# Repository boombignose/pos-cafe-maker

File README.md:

<div align="center">

# POS Café Maker
## ระบบร้านคาเฟ่บน Windows พร้อมพิมพ์เขียวเครื่อง POS

**ระบบร้านบน PostgreSQL · หลายหน้าจอใน LAN · ไม่ใช้ Docker · เคส 3D และ KiCad แก้ต่อได้**

แจกแบบ CAD และ source ที่ใช้งานแก้ไขได้ พร้อม [ที่มาข้อมูลและใบบันทึกอุปกรณ์](docs/BLUEPRINT.md) ขนาดจอเริ่มต้นอ้างอิง Waveshare 7inch HDMI LCD (C) จากเอกสารผู้ผลิต บอร์ดทั่วไป/พัดลมเป็นแม่แบบขนาดสมมติ ส่วนขอบบอร์ด รูและ net ของ PCB accessory มาจาก KiCad ใน repo ต้องตรวจอุปกรณ์จริงก่อนผลิต

รุ่น 0.1.2 เก็บมุมเคส ฐานเป็นแท่นรองด้านหลังขันยึดกับฝา มีตัวประคองขอบหลังจอและช่องรัดสาย หน้าขายใช้ปุ่มเมนูแบบข้อความและตะกร้าชำระเงินในพื้นที่จอ 1024×600 ดู [วิธีประกอบ](docs/PRINTING.md) แบบยังไม่ผ่านการประกอบจริง

[เปิดเดโมออนไลน์](https://boombignose.github.io/pos-cafe-maker/) · [เริ่มใช้](#quick-start) · [ออกแบบและพิมพ์](docs/DESIGNER.md) · [วงจรและ PCB](docs/HARDWARE.md) · [ผลตรวจ](docs/TEST-REPORT.md)

[ดาวน์โหลด Source ZIP](https://github.com/boombignose/pos-cafe-maker/archive/refs/heads/main.zip) · [ชุดระบบร้านและเดโม](https://github.com/boombignose/pos-cafe-maker/releases/tag/v0.2.0)

</div>

> **เลือกให้ตรงโหมด:** `shop ZIP` เป็นระบบร้านที่ใช้ฐานข้อมูลกลางและบัญชีจริง ส่วนเว็บ Pages และ `demo ZIP` เป็นข้อมูลจำลองใน browser ทั้งคู่ใช้ซอร์สเดียวกัน แต่แยกชุด build ชัดเจน เคส/PCB ยังไม่ผ่านการผลิตและประกอบจริง

## ใช้ระบบร้านบน Windows

1. ติดตั้ง [Node.js 24 LTS](https://nodejs.org/en/download) และ [PostgreSQL 17 หรือ18](https://www.postgresql.org/download/windows/) จากผู้ผลิต
2. ดาวน์โหลด `pos-cafe-maker-shop-v0.2.0.zip` จาก [Release](https://github.com/boombignose/pos-cafe-maker/releases/tag/v0.2.0) แตกไฟล์ แล้วดับเบิลคลิก **Start.cmd** ครั้งแรกต้องมีอินเทอร์เน็ตเพื่อติดตั้ง npm dependencies ไม่มี API key หรือ Docker
3. ใช้รหัสใน `SETUP-TOKEN.txt` ที่เครื่องร้านตั้งชื่อร้านและบัญชีเจ้าของผ่านเว็บ ไม่มีรหัสเริ่มต้นร่วมกัน เพิ่มวัตถุดิบ/เมนู/บัญชีทีมตามร้านจริง แล้วเปิดกะ
4. เครื่องลูกเปิด URL LAN ที่ Start แสดง ข้อมูลอยู่ PostgreSQL ของเครื่องกลาง รีสตาร์ต/เปลี่ยนโฟลเดอร์โปรแกรมแล้วข้อมูลยังอยู่ สำรองผ่านหน้า **ตั้งค่าร้าน** หรือ Backup.cmd กู้เข้า database ใหม่โดยเก็บต้นฉบับไว้

อ่าน [คู่มือติดตั้ง LAN สำรอง กู้คืน และอัปเดต](docs/INSTALL.md) ก่อนใช้ HTTP ไม่เข้ารหัสข้อมูลระหว่างเครื่อง ใช้เฉพาะเครือข่ายร้านที่เชื่อถือได้หรือให้ผู้ดูแลติดตั้ง HTTPS ผลตรวจโปรแกรมไม่แทนการทดสอบเครื่องพิมพ์และการทดลองร้านของคุณ

สำหรับผู้ที่ต้องการเตรียม Docker มี [คู่มือติดตั้ง Docker Desktop และ WSL 2 บน Windows](docs/DOCKER-WINDOWS.md) พร้อมตรวจ engine/Compose และแก้ปัญหาเบื้องต้น คู่มือนี้ยังไม่ใช่ชุดรัน POS ด้วย Docker; รุ่นนี้ใช้ `Start.cmd` ตามขั้นตอนข้างบน

ภาพเป็นรายการทดสอบบนฐานข้อมูลจริง ไม่ใช่ยอดขายหรือเงินที่รับจากลูกค้าจริง

## ในชุดนี้มีอะไร

| ออกแบบเครื่อง | ลองขายคาเฟ่ | วงจรเสริม | ส่งต่อทำของจริง |
|---|---|---|---|
| ขนาดจอ/เคส · บอร์ด · รูยึด · ช่องพอร์ต · มุมฐาน | เมนู/ตัวเลือก · เงินสด/โอนจำลอง · คิวบาร์ · กะ · สต็อกสูตร · CSV | บอร์ดเสริม 5V · ฟิวส์ · ป้องกันกลับขั้ว · พัดลม · ไฟสถานะ | STL แยก4ชิ้น · JSON · KiCad · BOM · Gerber · drill · STEP |

### ลองเดโม / พัฒนาจากซอร์ส

ต้องมี **Node.js 22.12+ หรือ Node.js 24 LTS** และ npm ไม่ต้องใส่ API key

```sh
git clone https://github.com/boombignose/pos-cafe-maker.git
cd pos-cafe-maker
npm ci
npm run dev
```

1. เปิด URL ที่ Vite แสดง โดยปกติ `http://localhost:5173` แล้วเข้า **ออกแบบเครื่อง** วัดขนาดอุปกรณ์จริงก่อนปรับแบบ
2. เข้า **หน้าขาย POS** → เปิดกะ → เลือกเมนู → รับเงินจำลอง → ออกคิว เลือกบทบาทด้านบนเพื่อลองแคชเชียร์หรือบาร์
3. ดาวน์โหลด STL/JSON จากหน้าออกแบบ เปิดใน slicer และดู [คู่มือ PCB](docs/HARDWARE.md) ก่อนสั่งพิมพ์หรือส่งผลิต

ถ้าดาวน์โหลด Source ZIP ให้แตกไฟล์ เปิด Terminal ในโฟลเดอร์นั้น แล้วเริ่มจาก `npm ci` หน้า HTML ต้องเปิดผ่านเว็บเซิร์ฟเวอร์ ไม่ใช่ดับเบิลคลิกซอร์ส `index.html`

### เดโม browser สำเร็จรูปจาก Release

ดาวน์โหลดไฟล์ `pos-cafe-maker-demo-v0.2.0.zip` แตกไฟล์ แล้วรัน:

```sh
cd pos-cafe-maker-demo
python3 -m http.server 8080 --bind 127.0.0.1
```

เปิด `http://localhost:8080` ไม่มี npm/Docker/ฐานข้อมูลสำหรับแพ็กเกจเดโมที่ build แล้ว ต้องดาวน์โหลดไฟล์นี้จาก Release ไม่ใช่ Source ZIP หน้าเว็บและข้อมูลจำลองทำงานได้โดยไม่ใช้บริการออนไลน์หลังดาวน์โหลด

## ลอง workflow ร้าน

ทั้งโหมดร้านและเดโม หน้าขายเลือกหมวดและเมนู เพิ่มจำนวน เลือกขนาด/ชนิดนม คำนวณเงินทอน และพิมพ์ใบเสร็จตัวอย่าง58/80มม. โหมดร้านพนักงานต้องตรวจยอดโอนจริงก่อนยืนยัน ส่วนเดโมจำลองการตรวจ ไม่มีการเชื่อมธนาคาร

คิวบาร์อัปเดตทุก2วินาที เริ่มทำ → พร้อมรับ → ส่งมอบ เจ้าของร้านดูเมนู/สูตร รับวัตถุดิบ ปรับสต็อกพร้อมเหตุผล ดูรายงานและคืนเงินทั้งบิลได้ สูตรและราคาของบิลเก่ายังอ้างอิงตอนขาย คืนวัตถุดิบเฉพาะคิวที่ยังไม่เริ่มทำ

**เฉพาะโหมดเดโม:** ข้อมูลเก็บใน `localStorage` ของ origin นี้ การล้างข้อมูลเว็บไซต์ เปลี่ยน browser/profile/port หรือกดรีเซ็ตเดโมอาจทำข้อมูลเดโมหาย บทบาทเป็นการจำลอง ไม่มีรหัสผ่านจริงหรือการรับรองความปลอดภัยหลายผู้ใช้ **อย่ากรอกรหัสผ่านหรือข้อมูลลูกค้าจริง** ข้อมูลจำลองไม่ส่งออกไปเซิร์ฟเวอร์

## ออกแบบเคสและ PCB

- จอและกล่องปรับเป็นมิลลิเมตร พรีวิวประกอบ/แยกชิ้น/โปร่งใส ใช้ geometry เดียวกับ STL
- วางบอร์ดและพัดลม ปรับรูยึด ตำแหน่ง/มุมหมุนในระนาบ PCB ช่องพอร์ตและพื้นที่เผื่อสาย ตรวจเตียงพิมพ์และพื้นที่ชน
- ส่งออก `frame.stl`, `body.stl`, `lid.stl`, `base.stl` และ `design.json` จอ บอร์ดและสายอ้างอิงไม่มีในไฟล์พิมพ์
- [ไฟล์ตัวอย่าง](examples/models/) และ [คู่มือวัด/พิมพ์](docs/DESIGNER.md) ค่าเริ่มต้นจอ164.90×106.96×8มม., active154.21×85.92มม. อ้างอิง [Waveshare 7inch HDMI LCD (C)](https://www.waveshare.com/wiki/7inch_HDMI_LCD_%28C%29) ยังต้องตรวจ revision พอร์ต แนว active area และพื้นที่กดล็อกของชิ้นจริง
- [บอร์ด PCB เสริม](hardware/sources/) มี source KiCad10, สัญลักษณ์/footprint ใน repo, [BOM](hardware/BOM.csv), ผังสาย และ [ไฟล์ผลิต](hardware/manufacturing/) แบบยังเป็นต้นแบบ
- ไฟDC5Vสำหรับพัดลม/LEDใช้บอร์ดเสริม คอมพิวเตอร์และจอใช้แหล่งจ่ายตามผู้ผลิตแยกกัน PCB นี้ไม่ใช่แหล่งจ่ายไฟ SBC และไม่ต่อไฟบ้าน
- เมื่อแก้ PCB ใช้เครื่องมือ [ส่งกลับ manifest](docs/HARDWARE.md) นำ JSON เข้าเว็บแล้วปรับรูยึด/พื้นที่ชิ้นส่วนใหม่ `STEP` ที่แจกเป็นตัวบอร์ดและทองแดง ส่วนชิ้นส่วนในเว็บเป็น envelope สำหรับเผื่อพื้นที่

## ตรวจและสร้างไฟล์เอง

```sh
npm test
npm run build
npm run models
python3 -m unittest discover -s tests -p 'hardware*_test.py'
python3 scripts/hardware/validate_export.py --check
python3 scripts/hardware/return_manifest.py hardware/sources/accessory.kicad_pcb hardware/board.json --check
```

[รายงานทดสอบ](docs/TEST-REPORT.md) แยกการตรวจเว็บ/geometry/ERC/DRC ออกจากการพิมพ์ ประกอบ โหลดไฟ และความร้อน ไม่มีหลักฐานการพิมพ์เคสหรือผลิตบอร์ดจริงในรุ่นนี้

## ระบบกลางและการพัฒนาต่อ

Express/PostgreSQL ใน `server/` เป็นระบบกลางของ shop mode เซิร์ฟเวอร์ตรวจสิทธิ์ owner/cashier/bar คิดราคาเอง เก็บเงินเป็นสตางค์ และทำ checkout/stock/refund ใน transaction พร้อม idempotency key และ row locks เมื่อคำตอบชำระหาย browser เก็บ intent เดิม ล็อกตะกร้า และตรวจผลเดิมหลัง reload/login ได้ เมื่อกู้ backup จะเปลี่ยน store epoch เพื่อห้ามส่งรายการค้างจากก่อนกู้ซ้ำ จนกว่าเจ้าของตรวจและบันทึกเหตุผล

พัฒนาจาก source ใช้ `npm ci` → `npm run build:shop` → `npm run shop` ส่วน `npm run build` ปกติยังเป็นเดโม [BACKEND.md](docs/BACKEND.md) อธิบาย API และการใช้ PostgreSQL ภายนอก [ผลตรวจ](docs/TEST-REPORT.md) แยก OS/ฐานข้อมูล/browser/ฮาร์ดแวร์อย่างชัดเจน

รุ่นแรก:ร้านเดียว ไม่มีโต๊ะ หลายสาขา payment gateway ใบกำกับภาษี offline checkout หรือ Windows service เครื่องพิมพ์ใบเสร็จผ่าน browser และไดรเวอร์ OS

## License

ซอฟต์แวร์และสคริปต์: [MIT](LICENSE) · แบบฮาร์ดแวร์/ไฟล์ผลิต/แบบตัวอย่าง: [CERN-OHL-P-2.0](hardware/LICENSE.md) พร้อม [ข้อความ license](LICENSES/CERN-OHL-P-2.0.txt) เอกสารผู้ผลิตและชื่อสินค้าเป็นของเจ้าของเดิม ดู [เครดิต dependencies](THIRD_PARTY.md)

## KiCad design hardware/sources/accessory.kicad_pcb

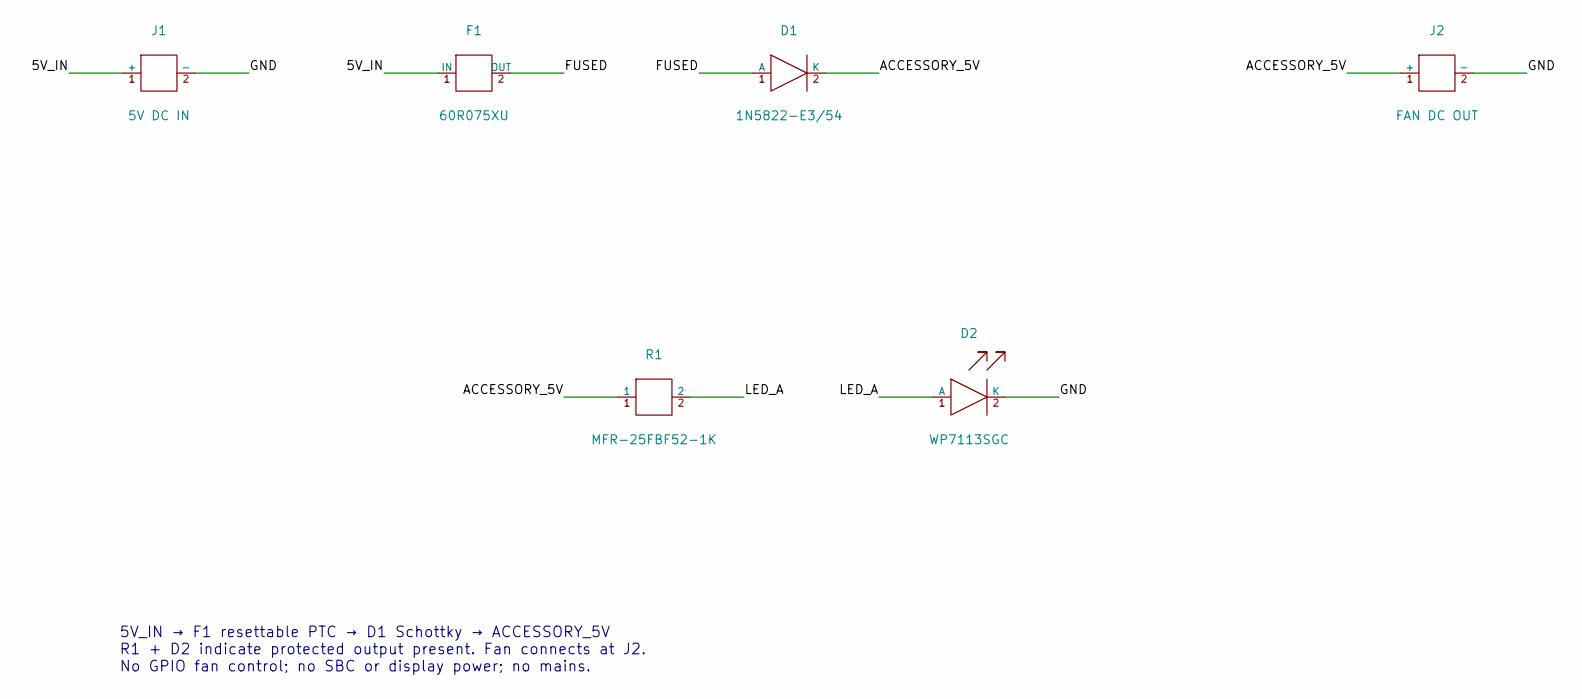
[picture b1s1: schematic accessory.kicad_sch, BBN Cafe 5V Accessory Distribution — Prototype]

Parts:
D1: 1N5822-E3/54; Axial_P15.24
D2: WP7113SGC; LED_D5
F1: 60R075XU; PTC_P5.08
J1: 5V DC IN; Terminal_5mm
J2: FAN DC OUT; Terminal_5mm
R1: MFR-25FBF52-1K; Resistor_P7.62

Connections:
/5V_IN: F1.1 (IN), J1.1 (+)
/ACCESSORY_5V: D1.2 (K), J2.1 (+), R1.1
/FUSED: D1.1 (A), F1.2 (OUT)
/GND: D2.2 (K), J1.2 (-), J2.2 (-)
/LED_A: D2.1 (A), R1.2

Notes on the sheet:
5V_IN → F1 resettable PTC → D1 Schottky → ACCESSORY_5V R1 + D2 indicate protected output present. Fan connects at J2. No GPIO fan control; no SBC or display power; no mains.

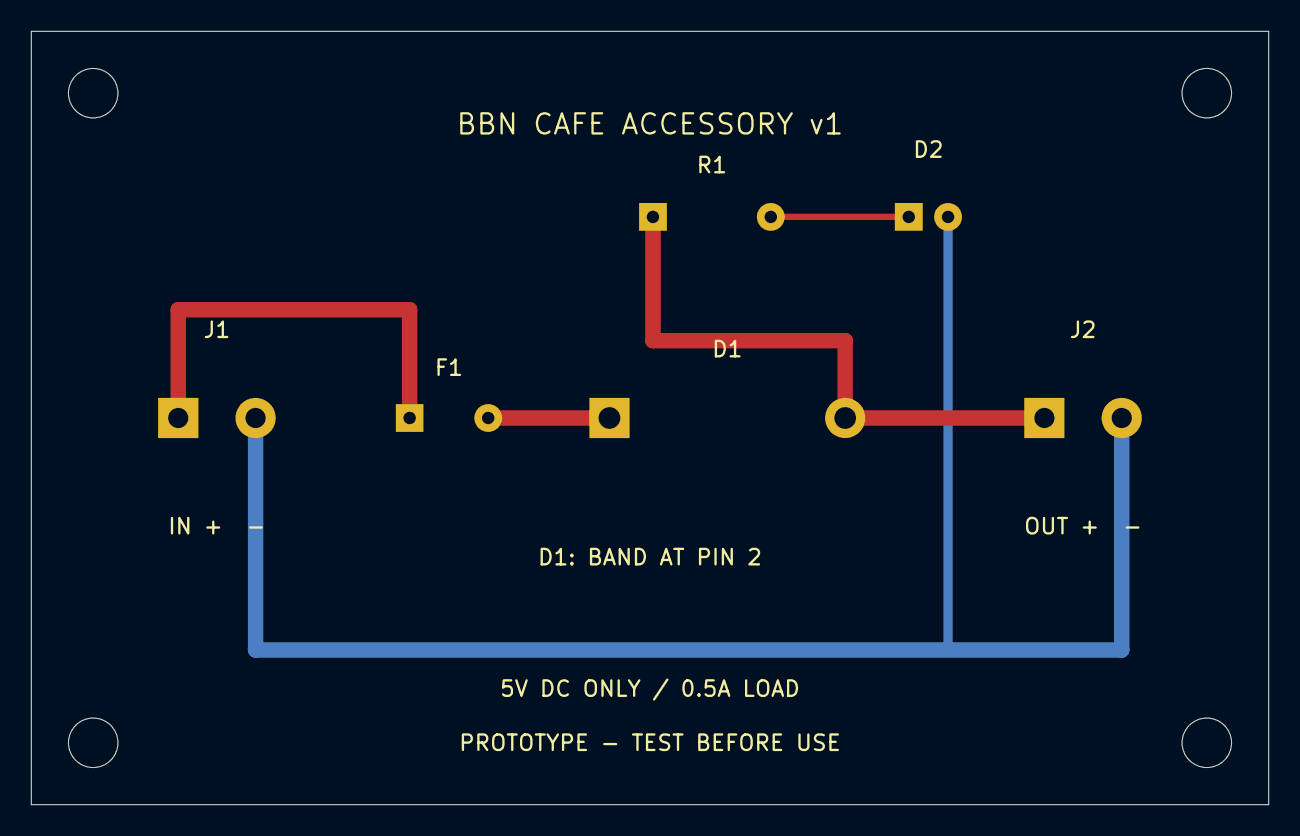
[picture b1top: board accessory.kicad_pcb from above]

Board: 2 copper layers, 80.0 x 50.0 mm, 10 parts (0 on the bottom side), 5 nets.

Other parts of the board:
H1, H2, H3, H4: M3 clearance; MountingHole_3.2mm
